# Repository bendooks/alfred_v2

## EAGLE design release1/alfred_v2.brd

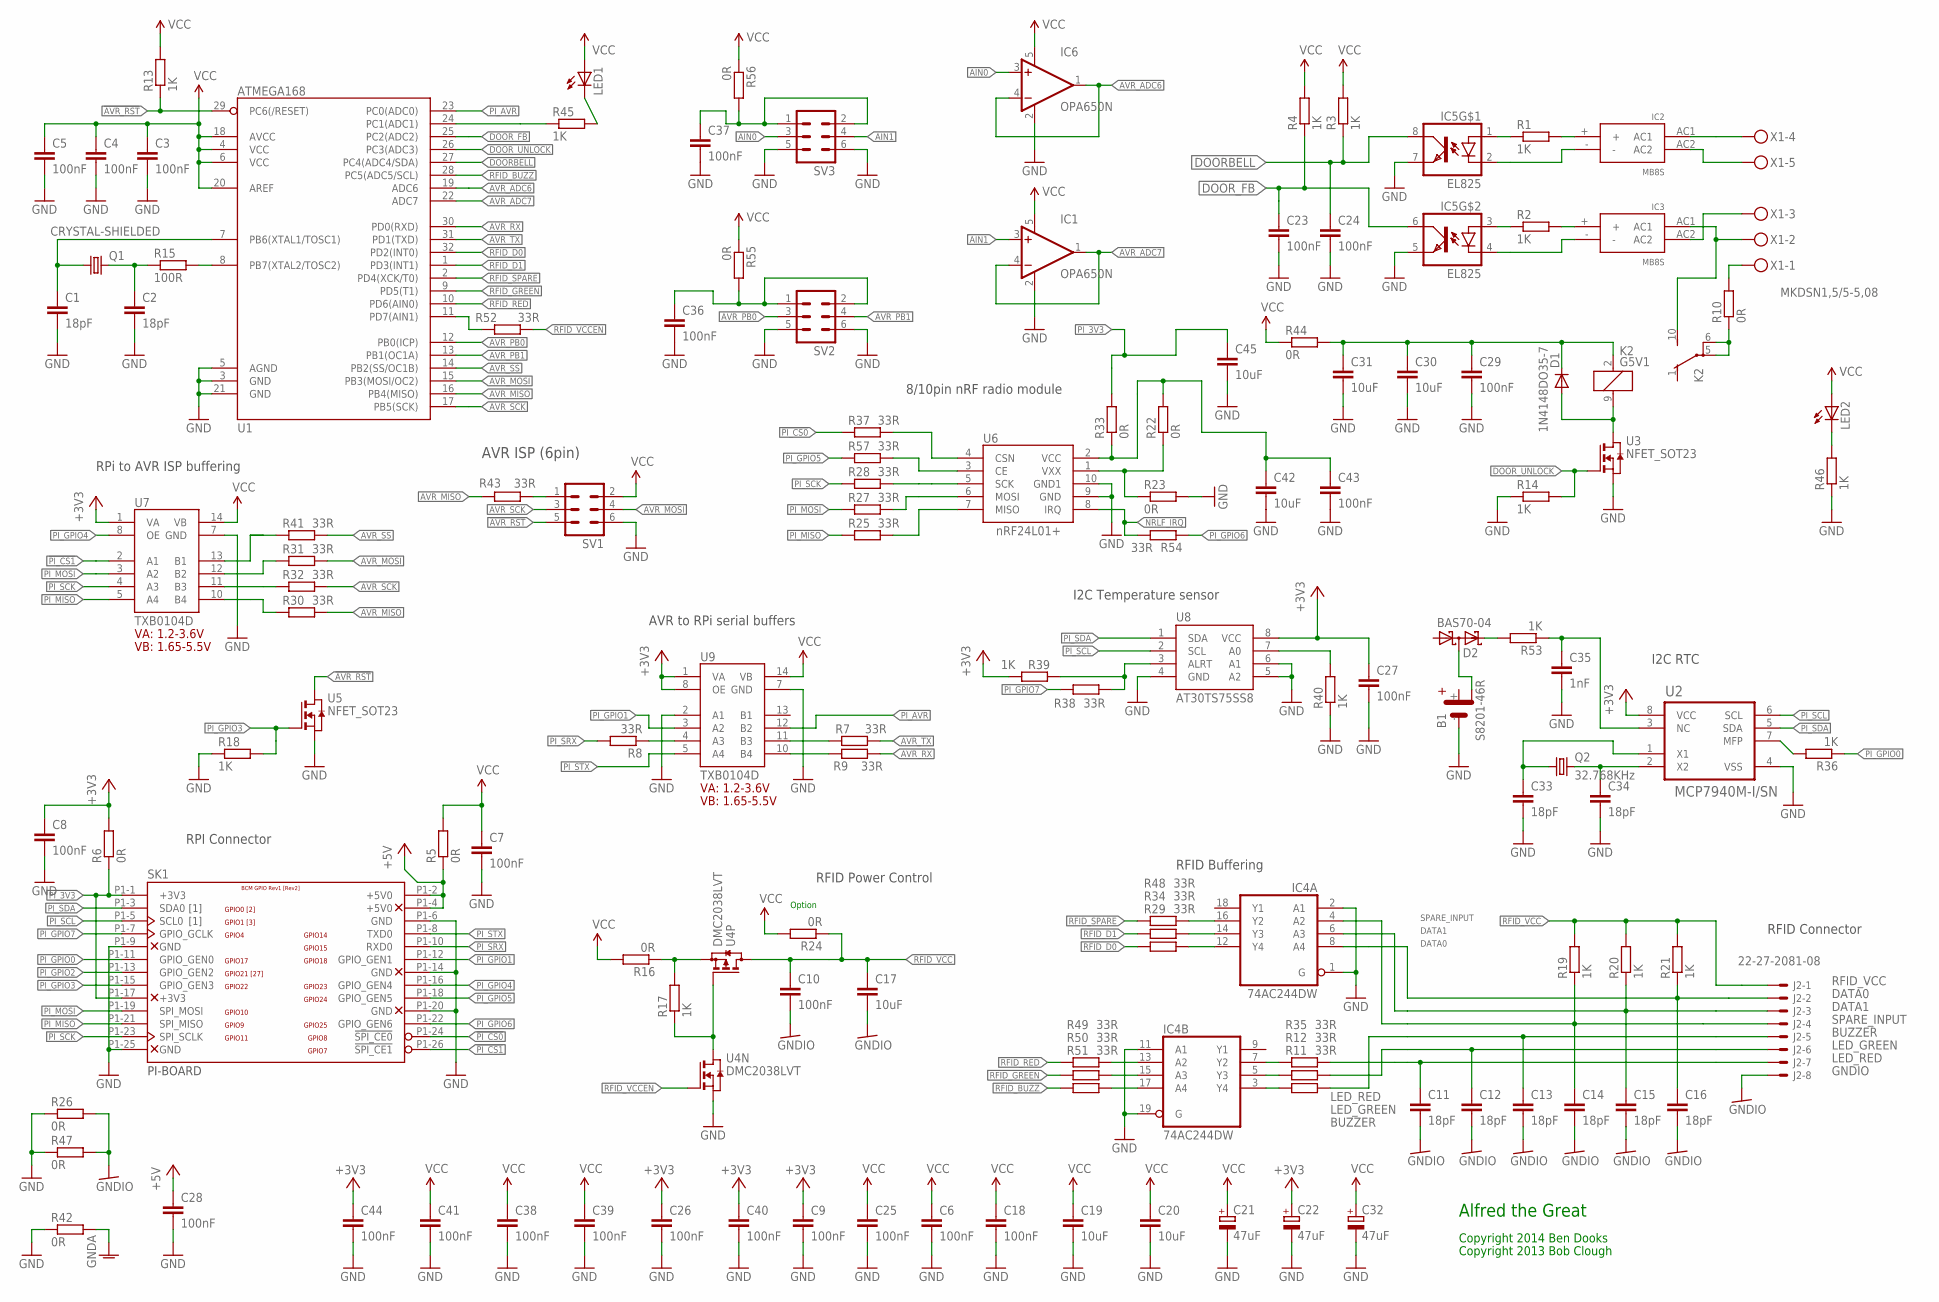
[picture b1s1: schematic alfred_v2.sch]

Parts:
B1: S8201-46R
C1, C2, C11, C12, C13, C14, C15, C16, C33, C34: 18pF; C0603K
C3, C4, C5, C6, C7, C8, C9, C10, C18, C23, C24, C25, C26, C27, C28, C29, C36, C37, C38, C39, C40, C41, C43, C44: 100nF; C0603K
C17, C19, C20, C30, C31, C42, C45: 10uF; C0805K
C21, C22, C32: 47uF; E2,5-7
C35: 1nF; C0603K
D1: 1N4148DO35-7; DO35-7
D2: BAS70-04; SOT23
IC1, IC6: OPA650N; SOT23-5
IC2, IC3: MB8S
IC4: 74AC244DW; SO20W
IC5: EL825; DIL08
J2: 22-27-2081-08; 6410-08
K2: G5V1
LED1, LED2: LEDSML0805; SML0805
Q1: CRYSTAL-SHIELDED; SMX4
Q2: 32.768KHz; TC26H
R1, R2, R3, R4, R13, R14, R17, R18, R36, R39, R40, R45, R46, R53: 1K; R0603
R5, R6, R10, R16, R22, R23, R24, R26, R33, R42, R44, R47, R55, R56: 0R; R0603
R7, R8, R9, R11, R25, R27, R28, R30, R31, R32, R37, R38, R41, R43, R54, R57: 33R; R0603
R12, R35: 33R; 0204/5
R15: 100R; R0603
R19, R20, R21: 1K; 0204/5
R29, R34, R48, R49, R50, R51, R52: 33R; 0207/12
SK1: PI-BOARD; RASPBERRY-PI
SV1, SV2, SV3: MA03-2
U1: ATMEGA168; TQFP32-08
U2: MCP7940M-I/SN; SOIC127P600X175-8N
U3, U5: NFET_SOT23; SOT23
U4: DMC2038LVT; TSOT26
U6: NRF24L01+CHINESE-10PIN; CHINESE-10PIN
U7, U9: TXB0104D; SO-14
U8: AT30TS75SS8; SOIC8
X1: MKDSN1,5/5-5,08

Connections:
!AVR_RST: R13.1, SV1.5, U1.29 (PC6(/RESET)), U5.3 (D)
!NRLF_CE: R57.2, U6.3 (CE)
!NRLF_CS: R37.2, U6.4 (CSN)
!PI_CS0: R37.1, SK1.P1-24 (!SPI_CE0)
!PI_CS1: SK1.P1-26 (!SPI_CE1), U7.2 (A1)
+3V3: C8.1, C9.1, C22.+, C26.1, C27.1, C40.1, C44.1, R6.2, R39.1, U2.8 (VCC), U7.1 (VA), U8.8 (VCC), U9.1 (VA), U9.8 (OE)
+5V: C28.1, R5.1, SK1.P1-2 (+5V0), SK1.P1-4 (+5V0)
AIN0: IC6.3 (+IN), SV3.3
AIN1: IC1.3 (+IN), SV3.4
AVR_ADC6: IC6.1 (OUT), IC6.4 (-IN), U1.19 (ADC6)
AVR_ADC7: IC1.1 (OUT), IC1.4 (-IN), U1.22 (ADC7)
AVR_MISO: R30.2, R43.1, U1.16 (PB4(MISO))
AVR_MOSI: R31.2, SV1.4, U1.15 (PB3(MOSI/OC2))
AVR_PB0: SV2.3, U1.12 (PB0(ICP))
AVR_PB1: SV2.4, U1.13 (PB1(OC1A))
AVR_RX: R9.2, U1.30 (PD0(RXD))
AVR_SCK: R32.2, SV1.3, U1.17 (PB5(SCK))
AVR_SS: R41.2, U1.14 (PB2(SS/OC1B))
AVR_TX: R7.2, U1.31 (PD1(TXD))
BUZZER: C13.1, J2.5, R11.2
DATA0: C16.1, IC4.8 (A4), J2.2, R21.1
DATA1: C15.1, IC4.6 (A3), J2.3, R20.1
DOORBELL: C24.1, IC5.8 (COL), R3.1, U1.27 (PC4(ADC4/SDA))
DOOR_FB: C23.1, IC5.6 (COL), R4.1, U1.25 (PC2(ADC2))
DOOR_UNLOCK: R14.2, U1.26 (PC3(ADC3)), U3.1 (G)
GND: B1.-, C1.2, C2.2, C3.2, C4.2, C5.2, C6.2, C7.2, C8.2, C9.2, C18.2, C19.2, C20.2, C21.-, C22.-, C23.2, C24.2, C25.2, C26.2, C27.2, C28.2, C29.2, C30.2, C31.2, C32.-, C33.2, C34.2, C35.2, C36.2, C37.2, C38.2, C39.2, C40.2, C41.2, C42.2, C43.2, C44.2, C45.2, IC1.2 (V-), IC4.1 (G), IC4.2 (A1), IC4.10 (GND), IC4.11 (A1), IC4.19 (G), IC5.5 (EMIT), IC5.7 (EMIT), IC6.2 (V-), Q1.2 (GND), Q1.4 (GND), R14.1, R18.1, R23.2, R26.1, R40.1, R42.1, R46.1, R47.1, SK1.P1-6 (GND), SK1.P1-9 (GND), SK1.P1-14 (GND), SK1.P1-20 (GND), SK1.P1-25 (GND), SV1.6, SV2.5, SV2.6, SV3.5, SV3.6, U1.3 (GND), U1.5 (AGND), U1.21 (GND), U2.4 (VSS), U3.2 (S), U4.5 (S), U5.2 (S), U6.9 (GND), U6.10 (GND1), U7.7 (GND), U8.4 (GND), U8.5 (A2), U8.6 (A1), U9.2 (A1), U9.7 (GND)
GNDA: R42.2
GNDIO: C10.2, C11.2, C12.2, C13.2, C14.2, C15.2, C16.2, C17.2, J2.8, R26.2, R47.2
LED_GREEN: C12.1, J2.6, R12.2
LED_RED: C11.1, J2.7, R35.2
unnamed: IC5.1 (A), R1.1
unnamed: IC2.-, IC5.2 (C)
unnamed: IC2.+, R1.2
unnamed: IC2.AC1, X1.4
unnamed: IC2.AC2, X1.5
unnamed: IC5.3 (A), R2.1
unnamed: IC3.+, R2.2
unnamed: IC3.-, IC5.4 (C)
unnamed: IC3.AC2, X1.3
unnamed: R15.2, U1.8 (PB7(XTAL2/TOSC2))
unnamed: C1.1, Q1.3 (1), U1.7 (PB6(XTAL1/TOSC1))
unnamed: C2.1, Q1.1 (2), R15.1
unnamed: IC3.AC1, K2.10 (S), X1.2
unnamed: R8.1, U9.4 (A3)
unnamed: R10.2, X1.1
unnamed: D1.A, K2.9 (2), U3.3 (D)
unnamed: IC4.16 (Y2), R48.2
unnamed: K2.5, K2.6, R10.1
unnamed: C35.1, R53.1, U2.3 (NC)
unnamed: D2.2 (C2), R53.2
unnamed: R43.2, SV1.1
unnamed: R52.1, U1.11 (PD7(AIN1))
unnamed: B1.+1 (+2), D2.3 (C1A2)
unnamed: IC4.14 (Y3), R34.2
unnamed: R30.1, U7.10 (B4)
unnamed: R36.2, U2.7 (MFP)
unnamed: R25.2, U6.7 (MISO)
unnamed: R38.2, R39.2, U8.3 (ALRT)
unnamed: R27.2, U6.6 (MOSI)
unnamed: R28.2, U6.5 (SCK)
unnamed: IC4.12 (Y4), R29.2
unnamed: IC4.17 (A4), R51.2
unnamed: R41.1, U7.13 (B1)
unnamed: C29.1, C30.1, C31.1, D1.C, K2.2 (1), R44.2
unnamed: C33.1, Q2.1, U2.1 (X1)
unnamed: R45.1, U1.24 (PC1(ADC1))
unnamed: LED1.C, R45.2
unnamed: LED2.C, R46.2
unnamed: C34.1, Q2.2, U2.2 (X2)
unnamed: IC4.15 (A3), R50.2
unnamed: IC4.13 (A2), R49.2
unnamed: C36.1, R55.2, SV2.1, SV2.2
unnamed: C37.1, R56.2, SV3.1, SV3.2
NRLF_IRQ: R54.2, U6.8 (IRQ)
PI_3V3: C45.1, R6.1, R33.2, SK1.P1-1 (+3V3), SK1.P1-17 (+3V3)
PI_AVR: U1.23 (PC0(ADC0)), U9.12 (B2)
PI_GPIO0: R36.1, SK1.P1-11 (GPIO_GEN0)
PI_GPIO1: SK1.P1-12 (GPIO_GEN1), U9.3 (A2)
PI_GPIO2: SK1.P1-13 (GPIO_GEN2)
PI_GPIO3: R18.2, SK1.P1-15 (GPIO_GEN3), U5.1 (G)
PI_GPIO4: SK1.P1-16 (GPIO_GEN4), U7.8 (OE)
PI_GPIO5: R57.1, SK1.P1-18 (GPIO_GEN5)
PI_GPIO6: R54.1, SK1.P1-22 (GPIO_GEN6)
PI_GPIO7: R38.1, SK1.P1-7 (GPIO_GCLK)
PI_MISO: R25.1, SK1.P1-21 (SPI_MISO), U7.5 (A4)
PI_MOSI: R27.1, SK1.P1-19 (SPI_MOSI), U7.3 (A2)
PI_SCK: R28.1, SK1.P1-23 (SPI_SCLK), U7.4 (A3)
PI_SCL: SK1.P1-5 (SCL0), U2.6 (SCL), U8.2 (SCL)
PI_SDA: SK1.P1-3 (SDA0), U2.5 (SDA), U8.1 (SDA)
PI_SRX: R8.2, SK1.P1-10 (RXD0)
PI_STX: SK1.P1-8 (TXD0), U9.5 (A4)
RFID_BUZZ: R51.1, U1.28 (PC5(ADC5/SCL))
RFID_D0: R29.1, U1.32 (PD2(INT0))
RFID_D1: R34.1, U1.1 (PD3(INT1))
RFID_GREEN: R50.1, U1.9 (PD5(T1))
RFID_RED: R49.1, U1.10 (PD6(AIN0))
RFID_SPARE: R48.1, U1.2 (PD4(XCK/T0))
RFID_SW: R17.1, U4.3 (G), U4.6 (D)
RFID_VCC: C10.1, C17.1, J2.1, R19.2, R20.2, R21.2, R24.1, U4.4 (D)
RFID_VCCEN: R52.2, U4.1 (G)
RFID_VCCSU: R16.1, R17.2, U4.2 (S)
RF_VCC: C42.1, C43.1, R22.2, R33.1, U6.2 (VCC)
RF_VXX: R22.1, R23.1, U6.1 (VXX)
R_BUZZER: IC4.3 (Y4), R11.1
R_GREEN: IC4.5 (Y3), R12.1
R_RED: IC4.7 (Y2), R35.1
SPARE_INPUT: C14.1, IC4.4 (A2), J2.4, R19.1
S_RX: R7.1, U9.11 (B3)
S_RX1: R32.1, U7.11 (B3)
S_TX: R9.1, U9.10 (B4)
S_TX1: R31.1, U7.12 (B2)
TMP_A0: R40.2, U8.7 (A0)
VCC: C3.1, C4.1, C5.1, C6.1, C7.1, C18.1, C19.1, C20.1, C21.+, C25.1, C32.+, C38.1, C39.1, C41.1, IC1.5 (V+), IC4.20 (VCC), IC6.5 (V+), LED1.A, LED2.A, R3.2, R4.2, R5.2, R13.2, R16.2, R24.2, R44.1, R55.1, R56.1, SV1.2, U1.4 (VCC), U1.6 (VCC), U1.18 (AVCC), U1.20 (AREF), U7.14 (VB), U9.14 (VB)

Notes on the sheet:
Option
Alfred the Great
Copyright 2014 Ben Dooks
Copyright 2013 Bob Clough
AVR to RPi serial buffers
RPi to AVR ISP buffering
RFID Connector
RFID Buffering
RFID Power Control
RPI Connector
I2C Temperature sensor
8/10pin nRF radio module
AVR ISP (6pin)
I2C RTC

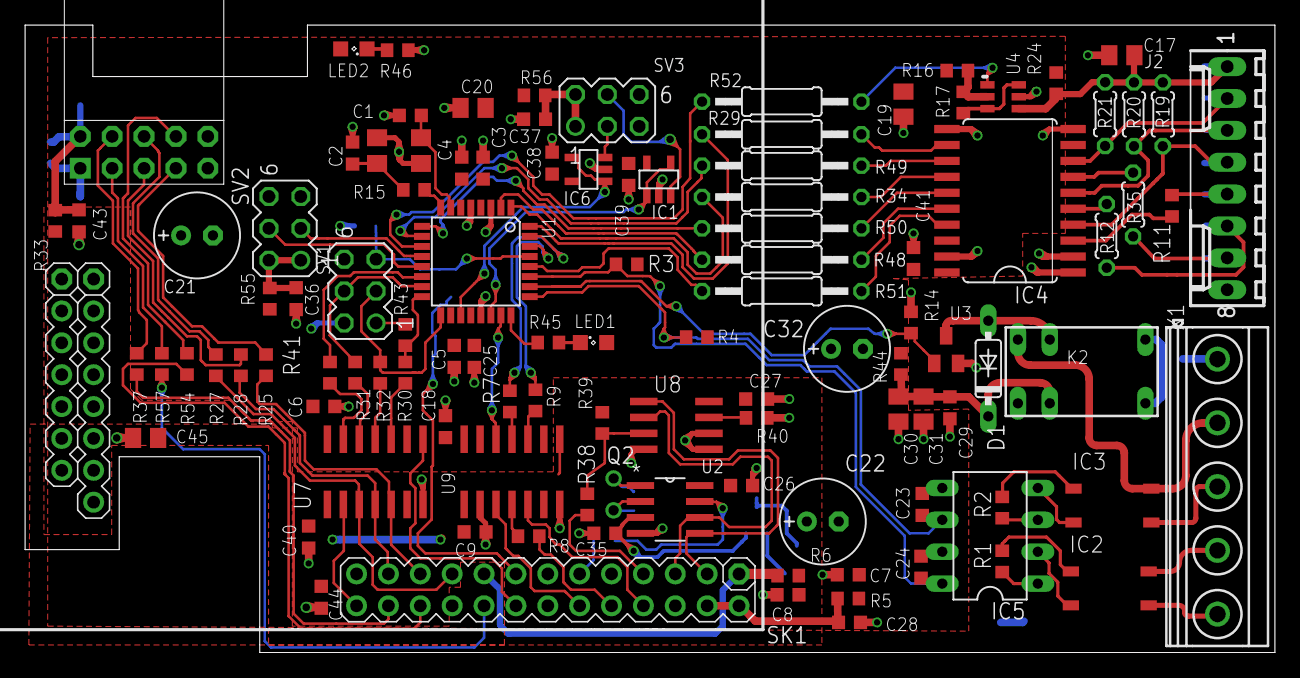
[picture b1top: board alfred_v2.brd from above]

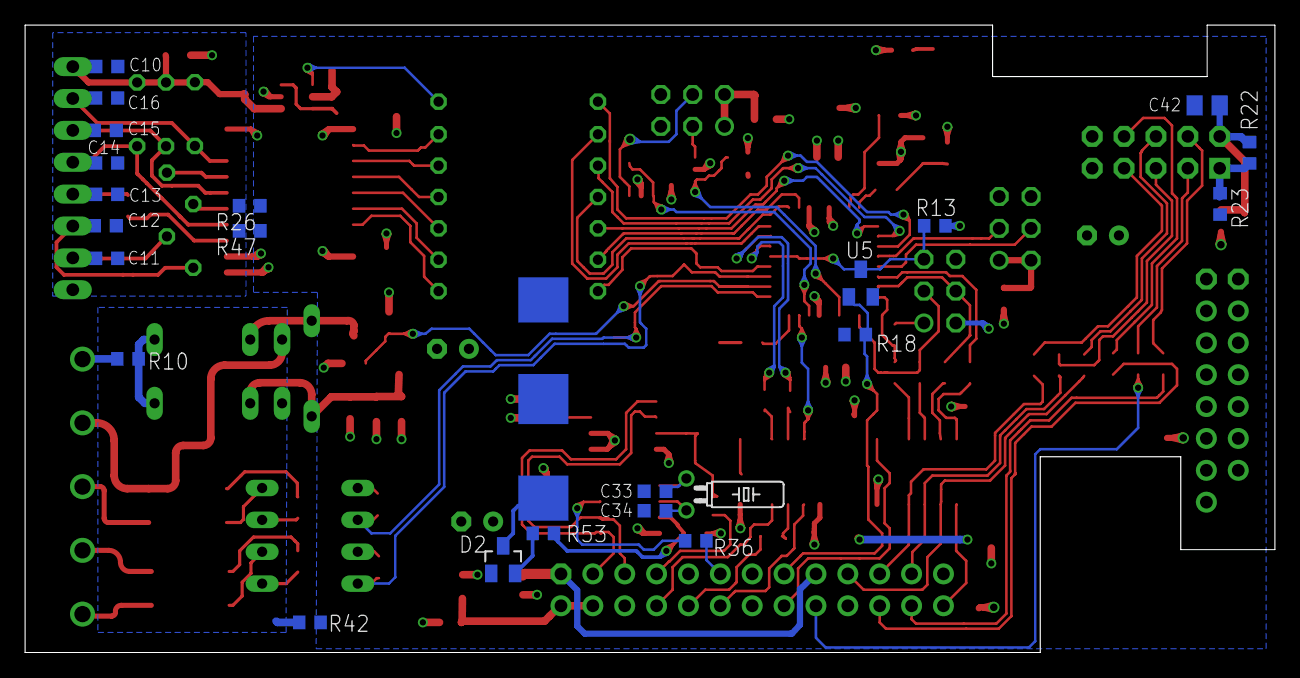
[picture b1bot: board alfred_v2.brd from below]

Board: 2 copper layers, 99.6 x 50.0 mm, 131 parts (24 on the bottom side), 111 nets.

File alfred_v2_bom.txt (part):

Partlist exported from /home/ben/eagle/Alfred_V2/alfred_v2.sch at 8/2/14 11:43 AM

Qty Value                  Device                 Package            Parts                                                                                                           Description                                                                               MF MPN              OC_FARNELL OC_NEWARK PACKAGE SUPPLIER 
2                          LEDSML0805             SML0805            LED1, LED2                                                                                                      LED                                                                                                                                                 
3                          MA03-2                 MA03-2             SV1, SV2, SV3                                                                                                   PIN HEADER                                                                                                    unknown    unknown                    
14  0R                     R-EU_R0603             R0603              R5, R6, R10, R16, R22, R23, R24, R26, R33, R42, R44, R47, R55, R56                                              RESISTOR, European symbol                                                                                                                           
1   100R                   R-EU_R0603             R0603              R15                                                                                                             RESISTOR, European symbol                                                                                                                           
24  100nF                  C-EUC0603K             C0603K             C3, C4, C5, C6, C7, C8, C9, C10, C18, C23, C24, C25, C26, C27, C28, C29, C36, C37, C38, C39, C40, C41, C43, C44 CAPACITOR, European symbol                                                                                                                          
7   10uF                   C-EUC0805K             C0805K             C17, C19, C20, C30, C31, C42, C45                                                                               CAPACITOR, European symbol                                                                                                                          
10  18pF                   C-EUC0603K             C0603K             C1, C2, C11, C12, C13, C14, C15, C16, C33, C34                                                                  CAPACITOR, European symbol                                                                                                                          
3   1K                     R-EU_0204/5            0204/5             R19, R20, R21                                                                                                   RESISTOR, European symbol                                                                                                                           
14  1K                     R-EU_R0603             R0603              R1, R2, R3, R4, R13, R14, R17, R18, R36, R39, R40, R45, R46, R53                                                RESISTOR, European symbol                                                                                                                           
1   1N4148DO35-7           1N4148DO35-7           DO35-7             D1                                                                                                              DIODE                                                                                                                                               
1   1nF                    C-EUC0603K             C0603K             C35                                                                                                             CAPACITOR, European symbol                                                                                                                          
1   22-27-2081-08          22-27-2081-08          6410-08            J2                                                                                                              CONNECTOR                                                                                                     unknown    unknown                    
1   32.768KHz              CRYSTALTC26H           TC26H              Q2                                                                                                              CRYSTAL                                                                                                       unknown    unknown                    
2   33R                    R-EU_0204/5            0204/5             R12, R35                                                                                                        RESISTOR, European symbol                                                                                                                           
7   33R                    R-EU_0207/12           0207/12            R29, R34, R48, R49, R50, R51, R52                                                                               RESISTOR, European symbol                                                                                                                           
16  33R                    R-EU_R0603             R0603              R7, R8, R9, R11, R25, R27, R28, R30, R31, R32, R37, R38, R41, R43, R54, R57                                     RESISTOR, European symbol                                                                                                                           
3   47uF                   CPOL-EUE2.5-7          E2,5-7             C21, C22, C32                                                                                                   POLARIZED CAPACITOR, European symbol                                                                                                                
1   74AC244DW              74AC244DW              SO20W              IC4                                                                                                             Octal BUFFER and LINE DRIVER, 3-state                                                                                                               
1   AT30TS75SS8            AT30TS75SS8            SOIC8              U8                                                                                                                                                                                                                                                                  
1   ATMEGA168              ATMEGA168              TQFP32-08          U1                                                                                                                                                                                                                                                                  
1   BAS70-04               BAS70-04               SOT23              D2                                                                                                              Silicon Schottky Diodes                                                                                                                             
1   CRYSTAL-SHIELDED       CRYSTAL-SHIELDED       SMX4               Q1                                                                                                                                                                                                                                                                  
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
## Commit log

2014-09-06 initial alfred project import
2014-09-06 alfred schematics
2014-09-06 alfred: add git ignore
2014-09-06 alfred: bom file
2014-09-06 alfred: test code
